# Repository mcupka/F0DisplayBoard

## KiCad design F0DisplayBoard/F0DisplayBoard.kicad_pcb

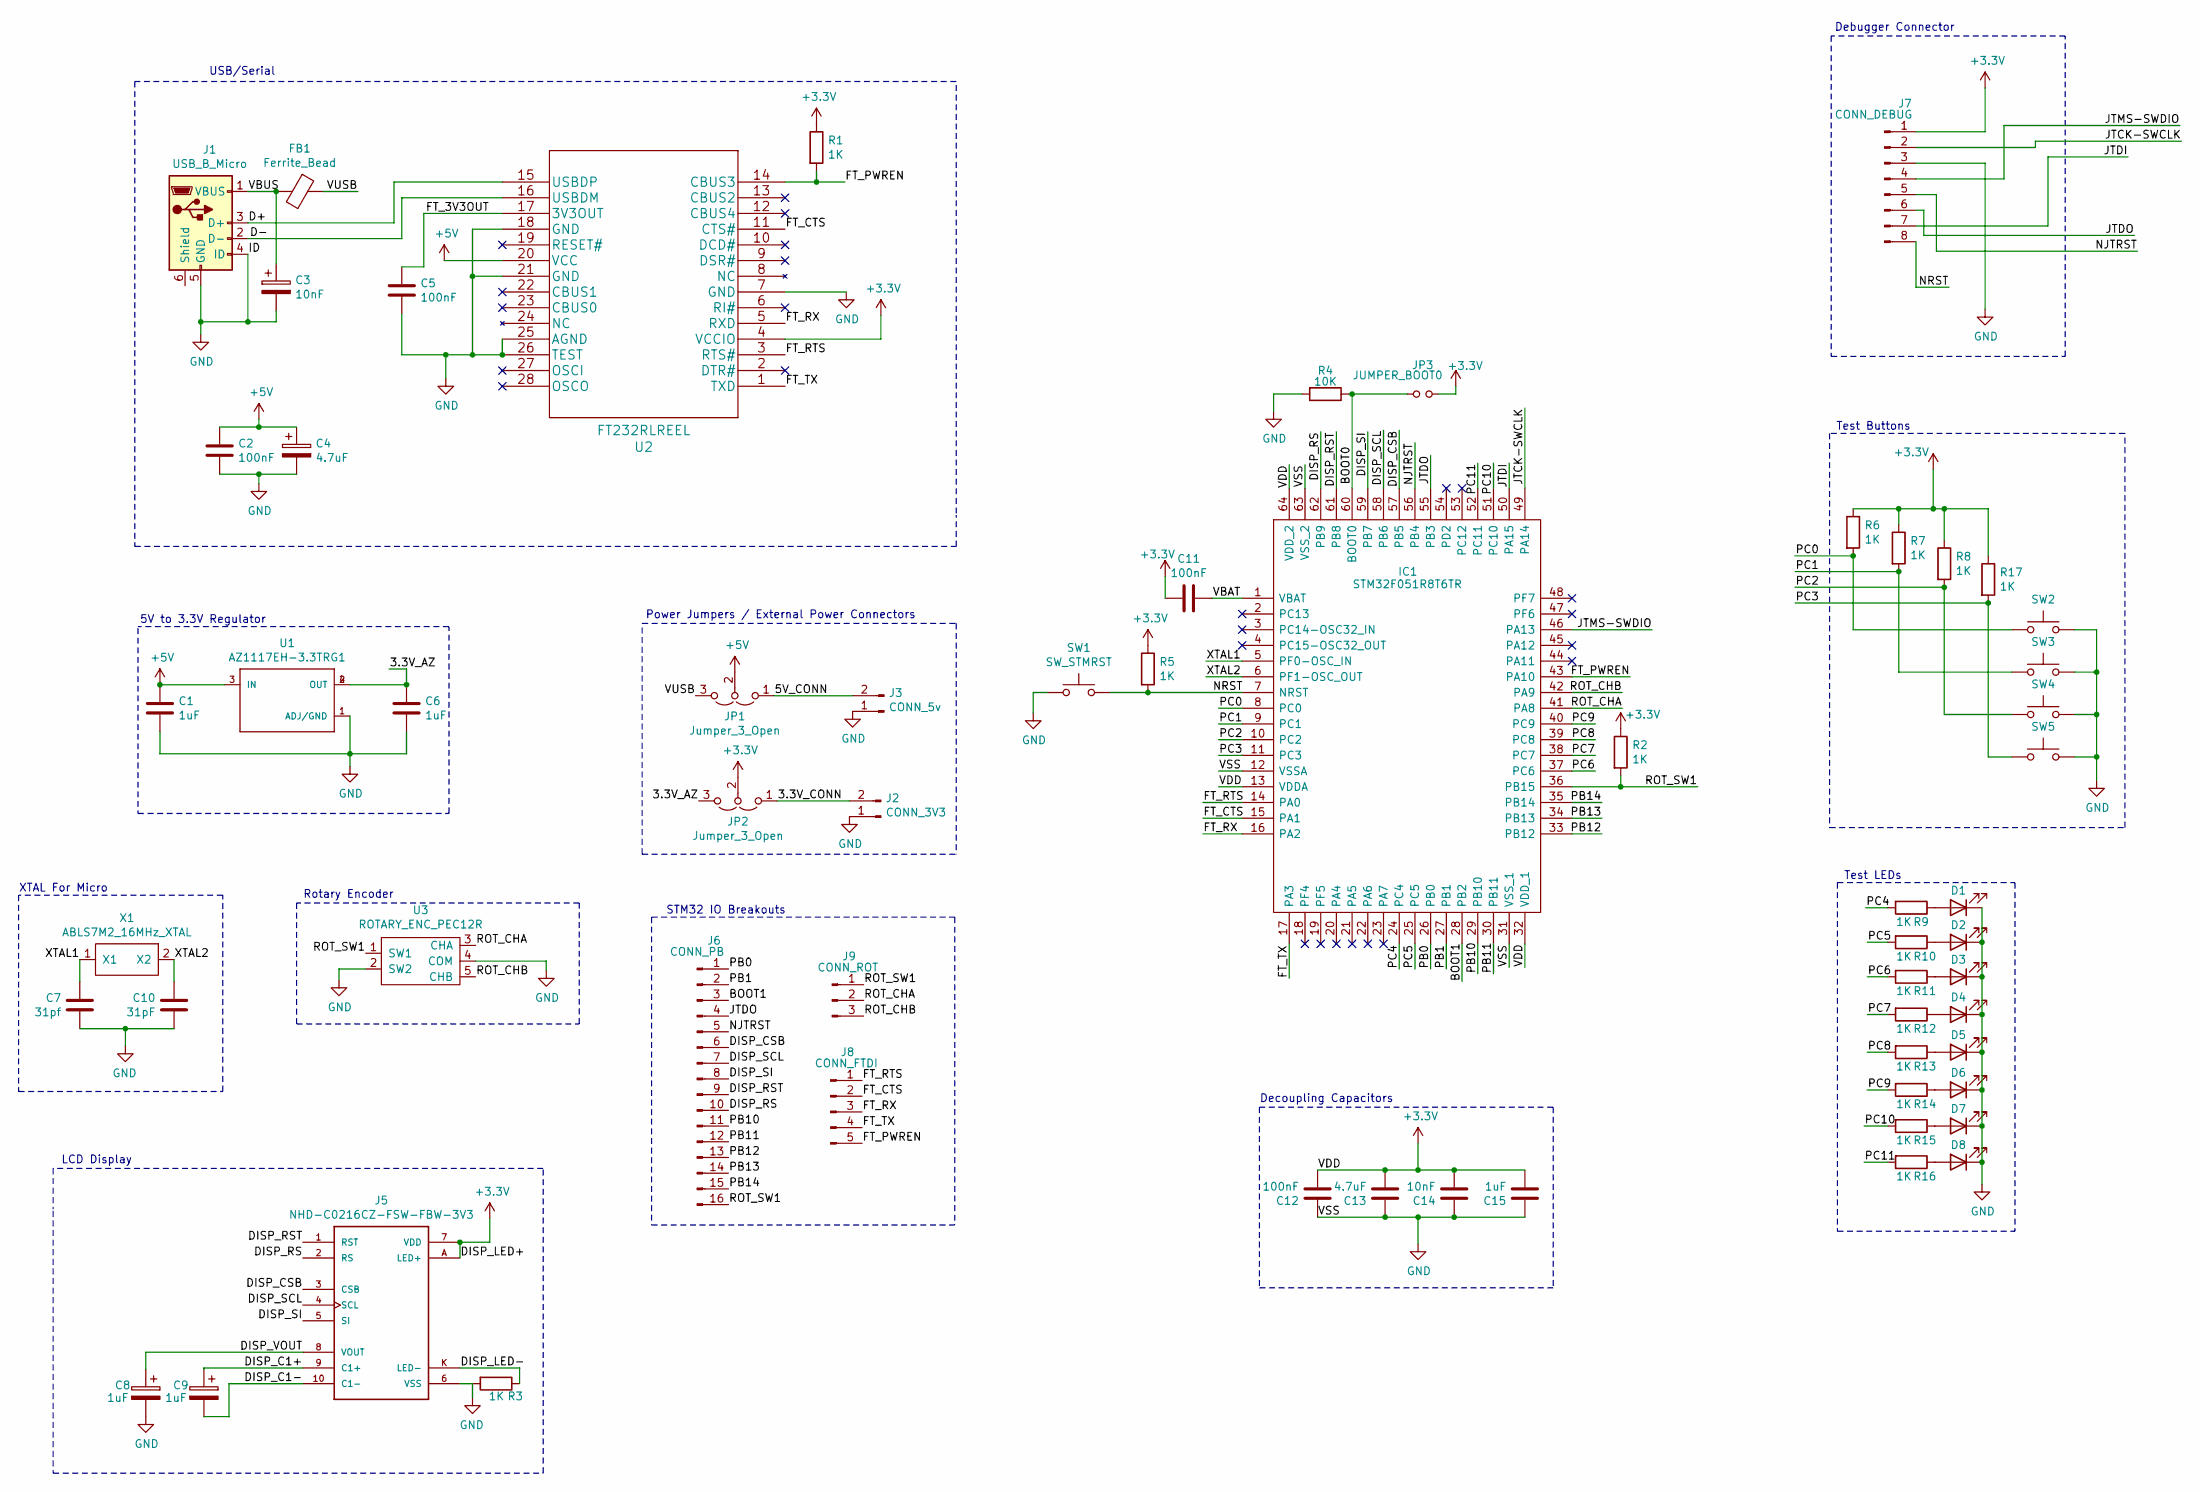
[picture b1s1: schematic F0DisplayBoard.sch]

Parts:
C1, C6, C8, C9, C15: 1uF; C_0805_2012Metric_Pad1.15x1.40mm_HandSolder
C2, C5, C11, C12: 100nF; C_0805_2012Metric_Pad1.15x1.40mm_HandSolder
C3, C14: 10nF; C_0805_2012Metric_Pad1.15x1.40mm_HandSolder
C4, C13: 4.7uF; C_0805_2012Metric_Pad1.15x1.40mm_HandSolder
C7: 31pf; C_0805_2012Metric_Pad1.15x1.40mm_HandSolder
C10: 31pF; C_0805_2012Metric_Pad1.15x1.40mm_HandSolder
D1, D2, D3, D4, D5, D6, D7, D8: LED; LED_0805_2012Metric_Pad1.15x1.40mm_HandSolder
FB1: Ferrite_Bead; R_0805_2012Metric_Pad1.15x1.40mm_HandSolder
IC1: STM32F051R8T6TR; QFP50P1200X1200X160-64N; Manufacturer_Part_Number STM32F051R8T6TR; Mouser Part Number 511-STM32F051R8T6TR
J1: USB_B_Micro; CUIDEVICES_UJ2-MIBH-4-SMT-TR
J2: CONN_3V3; PinHeader_1x02_P2.54mm_Vertical
J3: CONN_5v; PinHeader_1x02_P2.54mm_Vertical
J5: NHD-C0216CZ-FSW-FBW-3V3; LCD_NHD-C0216CZ-FSW-FBW-3V3
J6: CONN_PB; PinHeader_1x16_P2.54mm_Vertical
J7: CONN_DEBUG; PinHeader_1x08_P2.54mm_Vertical
J8: CONN_FTDI; PinHeader_1x05_P2.54mm_Vertical
J9: CONN_ROT; PinHeader_1x03_P2.54mm_Vertical
JP1, JP2: Jumper_3_Open; PinHeader_1x03_P2.54mm_Vertical
JP3: JUMPER_BOOT0; PinHeader_1x02_P2.54mm_Vertical
R1, R2, R3, R5, R6, R7, R8, R9, R10, R11, R12, R13, R14, R15, R16, R17: 1K; R_0805_2012Metric_Pad1.15x1.40mm_HandSolder
R4: 10K; R_0805_2012Metric_Pad1.15x1.40mm_HandSolder
SW1: SW_STMRST; PTS645SK43SMTR92LFS
SW2, SW3, SW4, SW5: SW_Push; PTS645SK43SMTR92LFS
U1: AZ1117EH-3.3TRG1; SOT230P700X180-4N
U2: FT232RLREEL
U3: ROTARY_ENC_PEC12R
X1: ABLS7M2_16MHz_XTAL; ABLS7M2

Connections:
+3V3: C11.2, C12.1, C13.1, C14.1, C15.1, IC1.13 (VDDA), IC1.32 (VDD_1), IC1.64 (VDD_2), J5.7 (VDD), J5.A (LED+), J7.1, JP2.2 (C), JP3.2, R1.1, R2.1, R5.1, R6.1, R7.1, R8.1, R17.1, U2.4 (VCCIO)
+5V: C1.1, C2.1, C4.1, JP1.2 (C), U1.3 (IN), U2.20 (VCC)
/3.3V_AZ: C6.1, JP2.3 (B), U1.2 (OUT), U1.4 (OUT)
/3.3V_CONN: J2.2, JP2.1 (A)
/5V_CONN: J3.2, JP1.1 (A)
/BOOT0: IC1.60 (BOOT0), JP3.1, R4.1
/BOOT1: IC1.28 (PB2), J6.3
/D+: J1.3 (D+), U2.15 (USBDP)
/D-: J1.2 (D-), U2.16 (USBDM)
/DISP_C1+: C9.1, J5.9 (C1+)
/DISP_C1-: C9.2, J5.10 (C1-)
/DISP_CSB: IC1.57 (PB5), J5.3 (CSB), J6.6
/DISP_LED-: J5.K (LED-), R3.1
/DISP_RS: IC1.62 (PB9), J5.2 (RS), J6.10
/DISP_RST: IC1.61 (PB8), J5.1 (RST), J6.9
/DISP_SCL: IC1.58 (PB6), J5.4 (SCL), J6.7
/DISP_SI: IC1.59 (PB7), J5.5 (SI), J6.8
/DISP_VOUT: C8.1, J5.8 (VOUT)
/FT_3V3OUT: C5.1, U2.17 (3V3OUT)
/FT_CTS: IC1.15 (PA1), J8.2, U2.11 (CTS#)
/FT_PWREN: IC1.43 (PA10), J8.5, R1.2, U2.14 (CBUS3)
/FT_RTS: IC1.14 (PA0), J8.1, U2.3 (RTS#)
/FT_RX: IC1.16 (PA2), J8.3, U2.5 (RXD)
/FT_TX: IC1.17 (PA3), J8.4, U2.1 (TXD)
/JTCK-SWCLK: IC1.49 (PA14), J7.2
/JTDI: IC1.50 (PA15), J7.7
/JTDO: IC1.55 (PB3), J6.4, J7.6
/JTMS-SWDIO: IC1.46 (PA13), J7.4
/NJTRST: IC1.56 (PB4), J6.5, J7.5
/NRST: IC1.7 (NRST), J7.8, R5.2, SW1.3, SW1.4
/PB0: IC1.26 (PB0), J6.1
/PB1: IC1.27 (PB1), J6.2
/PB10: IC1.29 (PB10), J6.11
/PB11: IC1.30 (PB11), J6.12
/PB12: IC1.33 (PB12), J6.13
/PB13: IC1.34 (PB13), J6.14
/PB14: IC1.35 (PB14), J6.15
/PC0: IC1.8 (PC0), R6.2, SW2.1, SW2.2
/PC1: IC1.9 (PC1), R7.2, SW3.1, SW3.2
/PC2: IC1.10 (PC2), R8.2, SW4.1, SW4.2
/PC3: IC1.11 (PC3), R17.2, SW5.1, SW5.2
/PC4: IC1.24 (PC4), R9.2
/PC5: IC1.25 (PC5), R10.2
/PC6: IC1.37 (PC6), R11.2
/PC7: IC1.38 (PC7), R12.2
/PC8: IC1.39 (PC8), R13.2
/PC9: IC1.40 (PC9), R14.2
/PC10: IC1.51 (PC10), R15.2
/PC11: IC1.52 (PC11), R16.2
/ROT_CHA: IC1.41 (PA8), J9.2, U3.3 (CHA)
/ROT_CHB: IC1.42 (PA9), J9.3, U3.5 (CHB)
/ROT_SW1: IC1.36 (PB15), J6.16, J9.1, R2.2, U3.1 (SW1)
/VBAT: C11.1, IC1.1 (VBAT)
/VBUS: C3.1, FB1.2, J1.1 (VBUS)
/VUSB: FB1.1, JP1.3 (B)
/XTAL1: C7.1, IC1.5 (PF0-OSC_IN), X1.1 (X1)
/XTAL2: C10.1, IC1.6 (PF1-OSC_OUT), X1.2 (X2)
GND: C1.2, C2.2, C3.2, C4.2, C5.2, C6.2, C7.2, C8.2, C10.2, C12.2, C13.2, C14.2, C15.2, D1.1 (K), D2.1 (K), D3.1 (K), D4.1 (K), D5.1 (K), D6.1 (K), D7.1 (K), D8.1 (K), IC1.12 (VSSA), IC1.31 (VSS_1), IC1.63 (VSS_2), J1.4 (ID), J1.5 (GND), J2.1, J3.1, J5.6 (VSS), J7.3, R3.2, R4.2, SW1.1, SW1.2, SW2.3, SW2.4, SW3.3, SW3.4, SW4.3, SW4.4, SW5.3, SW5.4, U1.1 (ADJ/GND), U2.7 (GND), U2.18 (GND), U2.21 (GND), U2.25 (AGND), U2.26 (TEST), U3.2 (SW2), U3.4 (COM)
unnamed: D1.2 (A), R9.1
unnamed: D2.2 (A), R10.1
unnamed: D3.2 (A), R11.1
unnamed: D4.2 (A), R12.1
unnamed: D5.2 (A), R13.1
unnamed: D6.2 (A), R14.1
unnamed: D7.2 (A), R15.1
unnamed: D8.2 (A), R16.1

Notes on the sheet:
5V to 3.3V Regulator
Rotary Encoder
XTAL For Micro
LCD Display
Power Jumpers / External Power Connectors
Debugger Connector
STM32 IO Breakouts
Test LEDs
Test Buttons
USB/Serial
Decoupling Capacitors

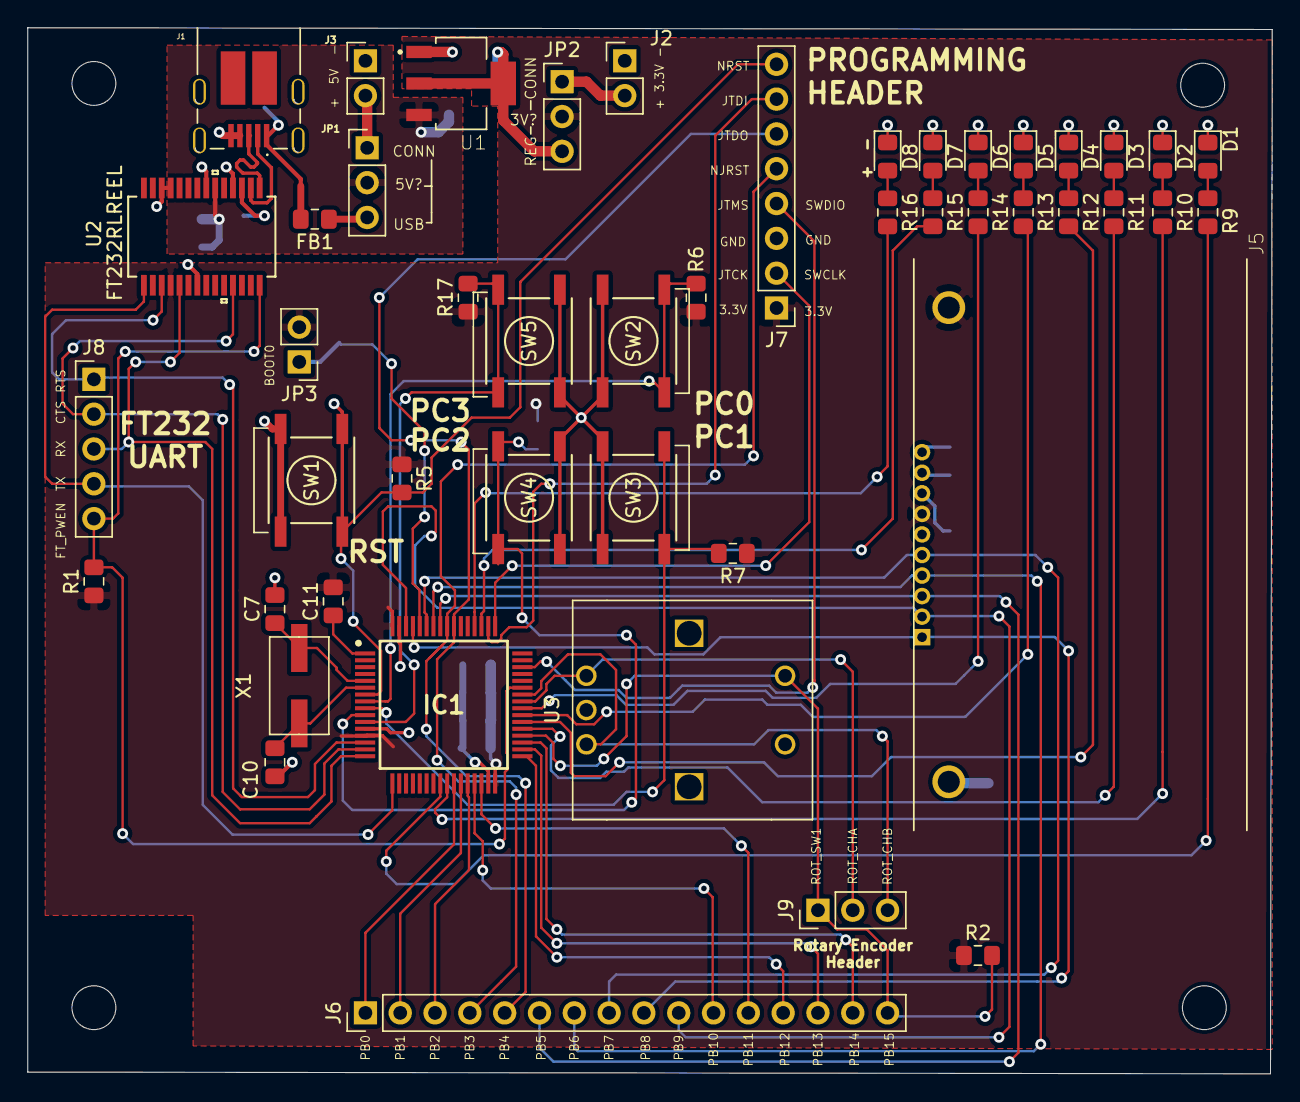
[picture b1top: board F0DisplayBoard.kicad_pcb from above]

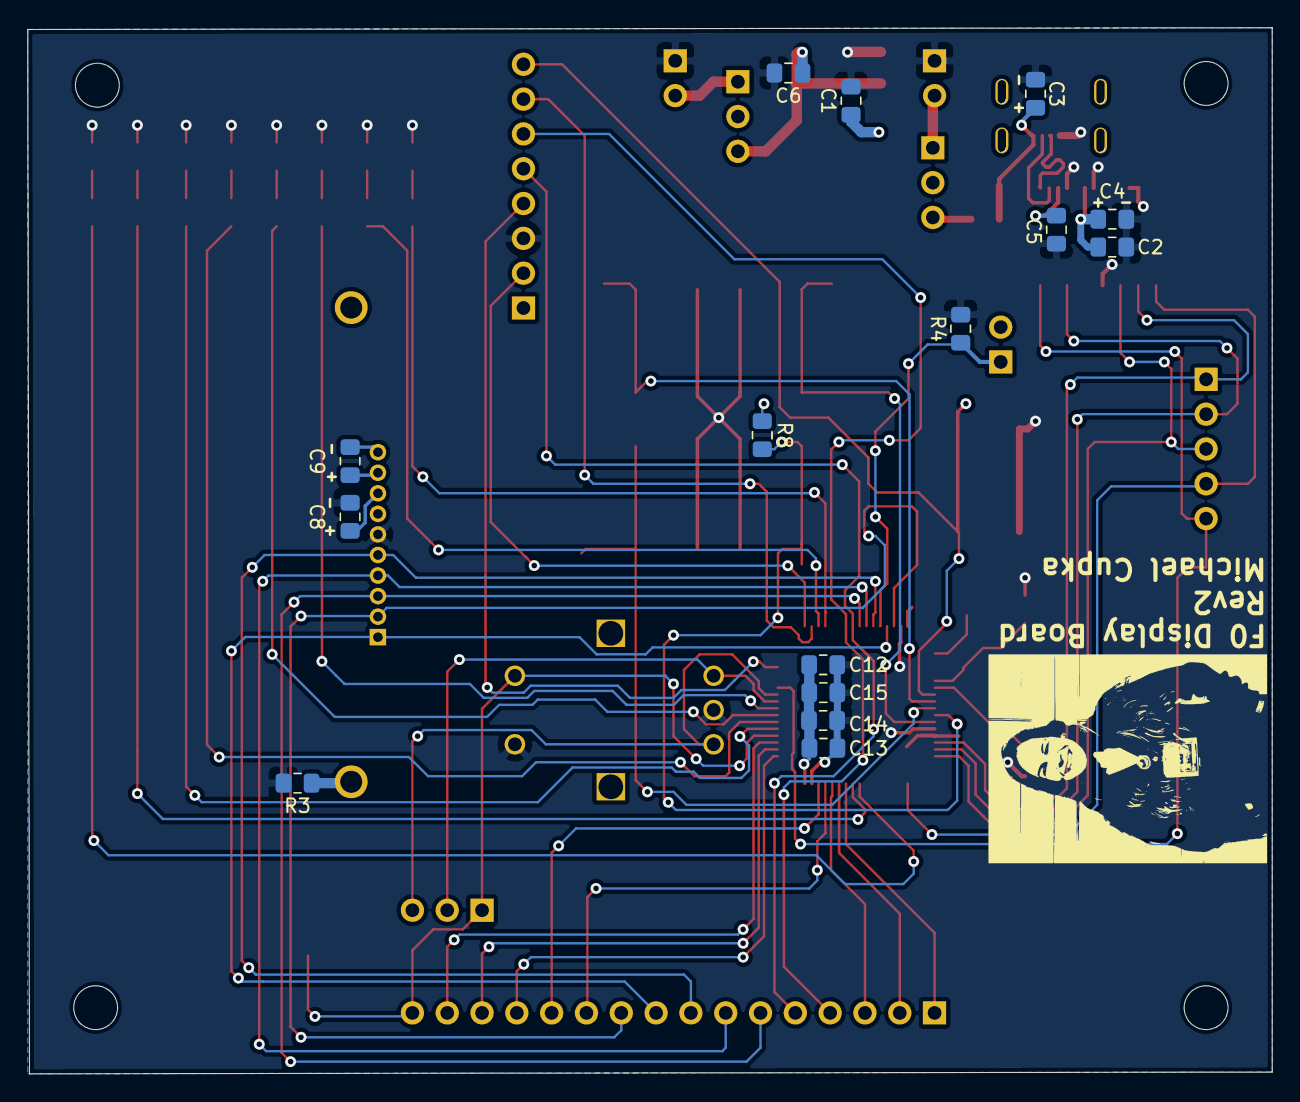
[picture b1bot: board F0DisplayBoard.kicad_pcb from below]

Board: 2 copper layers, 90.8 x 76.3 mm, 62 parts (15 on the bottom side), 66 nets.

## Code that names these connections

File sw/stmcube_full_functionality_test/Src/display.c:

#ifndef DISPLAY_C
#define DISPLAY_C

#include "display.h"
#include "main.h"
#include "usart.h"

void display_setup() {

	//Enable GPIO to use with display
	RCC->AHBENR |= RCC_AHBENR_GPIOBEN;
	GPIOB->MODER &= ~(GPIO_MODER_MODER5 | GPIO_MODER_MODER6 | GPIO_MODER_MODER7 | GPIO_MODER_MODER8 | GPIO_MODER_MODER9);
	GPIOB->MODER |= (GPIO_MODER_MODER5_0 | GPIO_MODER_MODER6_0 | GPIO_MODER_MODER7_0 | GPIO_MODER_MODER8_0 | GPIO_MODER_MODER9_0);

	//PB5 -> CSB (Active-low)
	//PB6 -> SCL
	//PB7 -> SI
	//PB8 -> RST
	//PB9 -> RS (Active-low)

	//Clear all of them. This also enables RST and CS since those are active-low
	GPIOB->ODR &= ~(GPIO_ODR_5 | GPIO_ODR_6 | GPIO_ODR_7 | GPIO_ODR_8 | GPIO_ODR_9);
	GPIOB->ODR |= GPIO_ODR_8; //Disable reset (active low)

	HAL_Delay(10);


	//initialize, turn on cursor, set address to 0
	uint8_t commands[] = {0x30, 0x30, 0x30, 0x39, 0x14, 0x56, 0x6D, 0x70, 0x0C, 0x06, 0x01, 0x0d, 0x80};

	for (int a = 0; a < (sizeof(commands) / sizeof(commands[0])); a++) {
		display_writecom((commands[a]));
	}

	//Disable CS (active-low)
	GPIOB->ODR |= GPIO_ODR_5;

}

void display_writecom(uint8_t transmitChar) {

	//make sure RS is low
	GPIOB->ODR &= ~(GPIO_ODR_9);

	//Transmit one 8-bit value to display
	for (int a = 0; a < 8; a++) {
		if ((transmitChar & 0x80) == 0x80) {
			//SDA high
			GPIOB->ODR |= GPIO_ODR_7;
		}
		else {
			//SDA low
			GPIOB->ODR &= ~(GPIO_ODR_7);
		}

		transmitChar <<= 1; //Shift bit out

		//Cycle SCL
		GPIOB->ODR |= GPIO_ODR_6;
		HAL_Delay(1);
		GPIOB->ODR &= ~(GPIO_ODR_6);

	}

}

void display_writedata(uint8_t transmitChar) {

	//make sure RS is high
	GPIOB->ODR |= GPIO_ODR_9;

	//Transmit one 8-bit value to display
	for (int a = 0; a < 8; a++) {
		if ((transmitChar & 0x80) == 0x80) {
			//SDA high
			GPIOB->ODR |= GPIO_ODR_7;
		}
		else {
			//SDA low
			GPIOB->ODR &= ~(GPIO_ODR_7);
		}

		transmitChar <<= 1; //Shift bit out

		//Cycle SCL
		GPIOB->ODR |= GPIO_ODR_6;
		HAL_Delay(1);
		GPIOB->ODR &= ~(GPIO_ODR_6);

	}

}

void display_print(uint8_t line, const char * text) {

	//Enable CS (active-low)
	GPIOB->ODR &= ~(GPIO_ODR_5);

	//line 2 starts after 40 characters
	uint8_t set_addr = 0x80 | (40 * line);

	display_writecom(set_addr);

	for (int a = 0; a < strlen(text); a++) {
		display_writedata((uint8_t)text[a]);
	}

	//Disable CS (active-low)
	GPIOB->ODR |= GPIO_ODR_5;

}

int display_present_menu(struct DisplayMenu menu, int (*nav_function)(), int (*sel_function)(), int start_index) {

	int highlighted = start_index;
	int selected = 0;
	int dir_up = 0;
	int navResult = 0;
	int cursorLine = 0;
	int updateDisplay = 0;

	display_clear();
	display_print(0, menu.options[highlighted]);
	display_print(1, menu.options[highlighted + 1]);

	while (selected == 0) {

		//only update display if something has changed
		if (updateDisplay == 1) {

			updateDisplay = 0;
			display_clear();

			//Display the two lines differently depending on if the bottom item it highlighted or the top item is highlighted
			if (dir_up == 0) {
				display_print(0, menu.options[highlighted]);
				if ((highlighted + 1) < menu.numOfOptions) display_print(1, menu.options[(highlighted + 1)]);
				else display_print(1, "------bottom----");
			}
			else {
				display_print(1, menu.options[highlighted]);
				if ((highlighted - 1) >= 0) display_print(0, menu.options[highlighted - 1]);
				else display_print(0, "-------top------");
			}

		}

	    //navigate menu until an option is selected
		navResult = nav_function();


		if (cursorLine == 1) dir_up = 1;
		else if (cursorLine == 0) dir_up = 0;



		if (navResult == 0) updateDisplay = 0;
		else if (highlighted + navResult >= menu.numOfOptions || highlighted < 0) updateDisplay = 0;
		else {
			highlighted += navResult;
			updateDisplay = 1;
		}

		if (cursorLine == 0 && navResult > 0) {
			updateDisplay = 0;
			cursorLine = 1;
		}
		else if (cursorLine == 1 && navResult < 0) {
			updateDisplay = 0;
			cursorLine = 0;
		}

		selected = sel_function();

		char loop_text[35] = "";
		snprintf(loop_text, sizeof(loop_text), "Encoder value: %5lu\r\n", TIM1->CNT);
		HAL_UART_Transmit(&huart2, (unsigned char *)loop_text, sizeof(loop_text), HAL_MAX_DELAY);


	}

	//error;
	return highlighted;
}

void display_clear() {
	display_print(0, "                ");
	display_print(1, "                ");
}


#endif //DISPLAY_C

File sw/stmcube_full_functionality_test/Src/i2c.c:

/**
  ******************************************************************************
  * File Name          : I2C.c
  * Description        : This file provides code for the configuration
  *                      of the I2C instances.
  ******************************************************************************
  * @attention
  *
  * <h2><center>&copy; Copyright (c) 2020 STMicroelectronics.
  * All rights reserved.</center></h2>
  *
  * This software component is licensed by ST under BSD 3-Clause license,
  * the "License"; You may not use this file except in compliance with the
  * License. You may obtain a copy of the License at:
  *                        opensource.org/licenses/BSD-3-Clause
  *
  ******************************************************************************
  */

/* Includes ------------------------------------------------------------------*/
#include "i2c.h"

/* USER CODE BEGIN 0 */

/* USER CODE END 0 */

I2C_HandleTypeDef hi2c1;

/* I2C1 init function */
void MX_I2C1_Init(void)
{

  hi2c1.Instance = I2C1;
  hi2c1.Init.Timing = 0x2000090E;
  hi2c1.Init.OwnAddress1 = 0;
  hi2c1.Init.AddressingMode = I2C_ADDRESSINGMODE_7BIT;
  hi2c1.Init.DualAddressMode = I2C_DUALADDRESS_DISABLE;
  hi2c1.Init.OwnAddress2 = 0;
  hi2c1.Init.OwnAddress2Masks = I2C_OA2_NOMASK;
  hi2c1.Init.GeneralCallMode = I2C_GENERALCALL_DISABLE;
  hi2c1.Init.NoStretchMode = I2C_NOSTRETCH_DISABLE;
  if (HAL_I2C_Init(&hi2c1) != HAL_OK)
  {
    Error_Handler();
  }
  /** Configure Analogue filter 
  */
  if (HAL_I2CEx_ConfigAnalogFilter(&hi2c1, I2C_ANALOGFILTER_ENABLE) != HAL_OK)
  {
    Error_Handler();
  }
  /** Configure Digital filter 
  */
  if (HAL_I2CEx_ConfigDigitalFilter(&hi2c1, 0) != HAL_OK)
  {
    Error_Handler();
  }

}

void HAL_I2C_MspInit(I2C_HandleTypeDef* i2cHandle)
{

  GPIO_InitTypeDef GPIO_InitStruct = {0};
  if(i2cHandle->Instance==I2C1)
  {
  /* USER CODE BEGIN I2C1_MspInit 0 */

  /* USER CODE END I2C1_MspInit 0 */
  
    __HAL_RCC_GPIOB_CLK_ENABLE();
    /**I2C1 GPIO Configuration    
    PB6     ------> I2C1_SCL
    PB7     ------> I2C1_SDA 
    */
    GPIO_InitStruct.Pin = DISP_SCL_Pin|DISP_SI_Pin;
    GPIO_InitStruct.Mode = GPIO_MODE_AF_OD;
    GPIO_InitStruct.Pull = GPIO_PULLUP;
    GPIO_InitStruct.Speed = GPIO_SPEED_FREQ_HIGH;
    GPIO_InitStruct.Alternate = GPIO_AF1_I2C1;
    HAL_GPIO_Init(GPIOB, &GPIO_InitStruct);

    /* I2C1 clock enable */
    __HAL_RCC_I2C1_CLK_ENABLE();
  /* USER CODE BEGIN I2C1_MspInit 1 */

  /* USER CODE END I2C1_MspInit 1 */
  }
}

void HAL_I2C_MspDeInit(I2C_HandleTypeDef* i2cHandle)
{

  if(i2cHandle->Instance==I2C1)
  {
  /* USER CODE BEGIN I2C1_MspDeInit 0 */

  /* USER CODE END I2C1_MspDeInit 0 */
    /* Peripheral clock disable */
    __HAL_RCC_I2C1_CLK_DISABLE();
  
    /**I2C1 GPIO Configuration    
    PB6     ------> I2C1_SCL
    PB7     ------> I2C1_SDA 
    */
    HAL_GPIO_DeInit(GPIOB, DISP_SCL_Pin|DISP_SI_Pin);

  /* USER CODE BEGIN I2C1_MspDeInit 1 */

  /* USER CODE END I2C1_MspDeInit 1 */
  }
} 

/* USER CODE BEGIN 1 */

/* USER CODE END 1 */

/************************ (C) COPYRIGHT STMicroelectronics *****END OF FILE****/

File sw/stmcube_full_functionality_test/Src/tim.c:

/**
  ******************************************************************************
  * File Name          : TIM.c
  * Description        : This file provides code for the configuration
  *                      of the TIM instances.
  ******************************************************************************
  * @attention
  *
  * <h2><center>&copy; Copyright (c) 2020 STMicroelectronics.
  * All rights reserved.</center></h2>
  *
  * This software component is licensed by ST under BSD 3-Clause license,
  * the "License"; You may not use this file except in compliance with the
  * License. You may obtain a copy of the License at:
  *                        opensource.org/licenses/BSD-3-Clause
  *
  ******************************************************************************
  */

/* Includes ------------------------------------------------------------------*/
#include "tim.h"

/* USER CODE BEGIN 0 */

/* USER CODE END 0 */

TIM_HandleTypeDef htim1;

/* TIM1 init function */
void MX_TIM1_Init(void)
{
  TIM_Encoder_InitTypeDef sConfig = {0};
  TIM_MasterConfigTypeDef sMasterConfig = {0};

  htim1.Instance = TIM1;
  htim1.Init.Prescaler = 0;
  htim1.Init.CounterMode = TIM_COUNTERMODE_UP;
  htim1.Init.Period = 65535;
  htim1.Init.ClockDivision = TIM_CLOCKDIVISION_DIV1;
  htim1.Init.RepetitionCounter = 0;
  htim1.Init.AutoReloadPreload = TIM_AUTORELOAD_PRELOAD_DISABLE;
  sConfig.EncoderMode = TIM_ENCODERMODE_TI12;
  sConfig.IC1Polarity = TIM_ICPOLARITY_RISING;
  sConfig.IC1Selection = TIM_ICSELECTION_DIRECTTI;
  sConfig.IC1Prescaler = TIM_ICPSC_DIV1;
  sConfig.IC1Filter = 0;
  sConfig.IC2Polarity = TIM_ICPOLARITY_RISING;
  sConfig.IC2Selection = TIM_ICSELECTION_DIRECTTI;
  sConfig.IC2Prescaler = TIM_ICPSC_DIV1;
  sConfig.IC2Filter = 0;
  if (HAL_TIM_Encoder_Init(&htim1, &sConfig) != HAL_OK)
  {
    Error_Handler();
  }
  sMasterConfig.MasterOutputTrigger = TIM_TRGO_RESET;
  sMasterConfig.MasterSlaveMode = TIM_MASTERSLAVEMODE_DISABLE;
  if (HAL_TIMEx_MasterConfigSynchronization(&htim1, &sMasterConfig) != HAL_OK)
  {
    Error_Handler();
  }

}

void HAL_TIM_Encoder_MspInit(TIM_HandleTypeDef* tim_encoderHandle)
{

  GPIO_InitTypeDef GPIO_InitStruct = {0};
  if(tim_encoderHandle->Instance==TIM1)
  {
  /* USER CODE BEGIN TIM1_MspInit 0 */

  /* USER CODE END TIM1_MspInit 0 */
    /* TIM1 clock enable */
    __HAL_RCC_TIM1_CLK_ENABLE();
  
    __HAL_RCC_GPIOA_CLK_ENABLE();
    /**TIM1 GPIO Configuration    
    PA8     ------> TIM1_CH1
    PA9     ------> TIM1_CH2 
    */
    GPIO_InitStruct.Pin = ROT_CHA_Pin|ROT_CHB_Pin;
    GPIO_InitStruct.Mode = GPIO_MODE_AF_PP;
    GPIO_InitStruct.Pull = GPIO_NOPULL;
    GPIO_InitStruct.Speed = GPIO_SPEED_FREQ_LOW;
    GPIO_InitStruct.Alternate = GPIO_AF2_TIM1;
    HAL_GPIO_Init(GPIOA, &GPIO_InitStruct);

  /* USER CODE BEGIN TIM1_MspInit 1 */

  /* USER CODE END TIM1_MspInit 1 */
  }
}

void HAL_TIM_Encoder_MspDeInit(TIM_HandleTypeDef* tim_encoderHandle)
{

  if(tim_encoderHandle->Instance==TIM1)
  {
  /* USER CODE BEGIN TIM1_MspDeInit 0 */

  /* USER CODE END TIM1_MspDeInit 0 */
    /* Peripheral clock disable */
    __HAL_RCC_TIM1_CLK_DISABLE();
  
    /**TIM1 GPIO Configuration    
    PA8     ------> TIM1_CH1
    PA9     ------> TIM1_CH2 
    */
    HAL_GPIO_DeInit(GPIOA, ROT_CHA_Pin|ROT_CHB_Pin);

  /* USER CODE BEGIN TIM1_MspDeInit 1 */

  /* USER CODE END TIM1_MspDeInit 1 */
  }
} 

/* USER CODE BEGIN 1 */

/* USER CODE END 1 */

/************************ (C) COPYRIGHT STMicroelectronics *****END OF FILE****/

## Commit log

2020-10-18 Initial Commit: -Basically done with the main schematic -Need to add test points/connectors/LEDs -Need to begin layout
2020-10-30 sch: Removed some connectors to make room on board. pcb: rough routing, difficulty with traces cutting into planes. May restart routing of most signals
2020-11-01 pcb: re-routed mostlyl orthogonally. Still need to get 3.3V plane to reach some pins and check other "unrouted" signals
2020-11-21 Rev2 completed -Added current-limiting resitstor for LCD backlight -Fixed microcontroller footprint -Board size reduced
2020-11-21 sw: started sw -simple uart print test completed using STMCubeMX, HAL, and SW4STM32
2020-12-04 sw: modified UART test to show interactive test menu -Created test to blink LEDs and added to menu
2020-12-15 pcb: added some dimensions
2020-12-15 3dcad: Added stand and case models. Designed using AutoCAD 2020 -Hole for programming header needs moved slightly. -Ridge needs widened / tab needs thinned. Currently, tab must be forced to fit into 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
2020-12-16 sw: started messing around with using the display module as a menu for running LED, encoder, display tests

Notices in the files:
parts and their libraries:
Copyright 2016 Accelerated Designs. All rights reserved.
